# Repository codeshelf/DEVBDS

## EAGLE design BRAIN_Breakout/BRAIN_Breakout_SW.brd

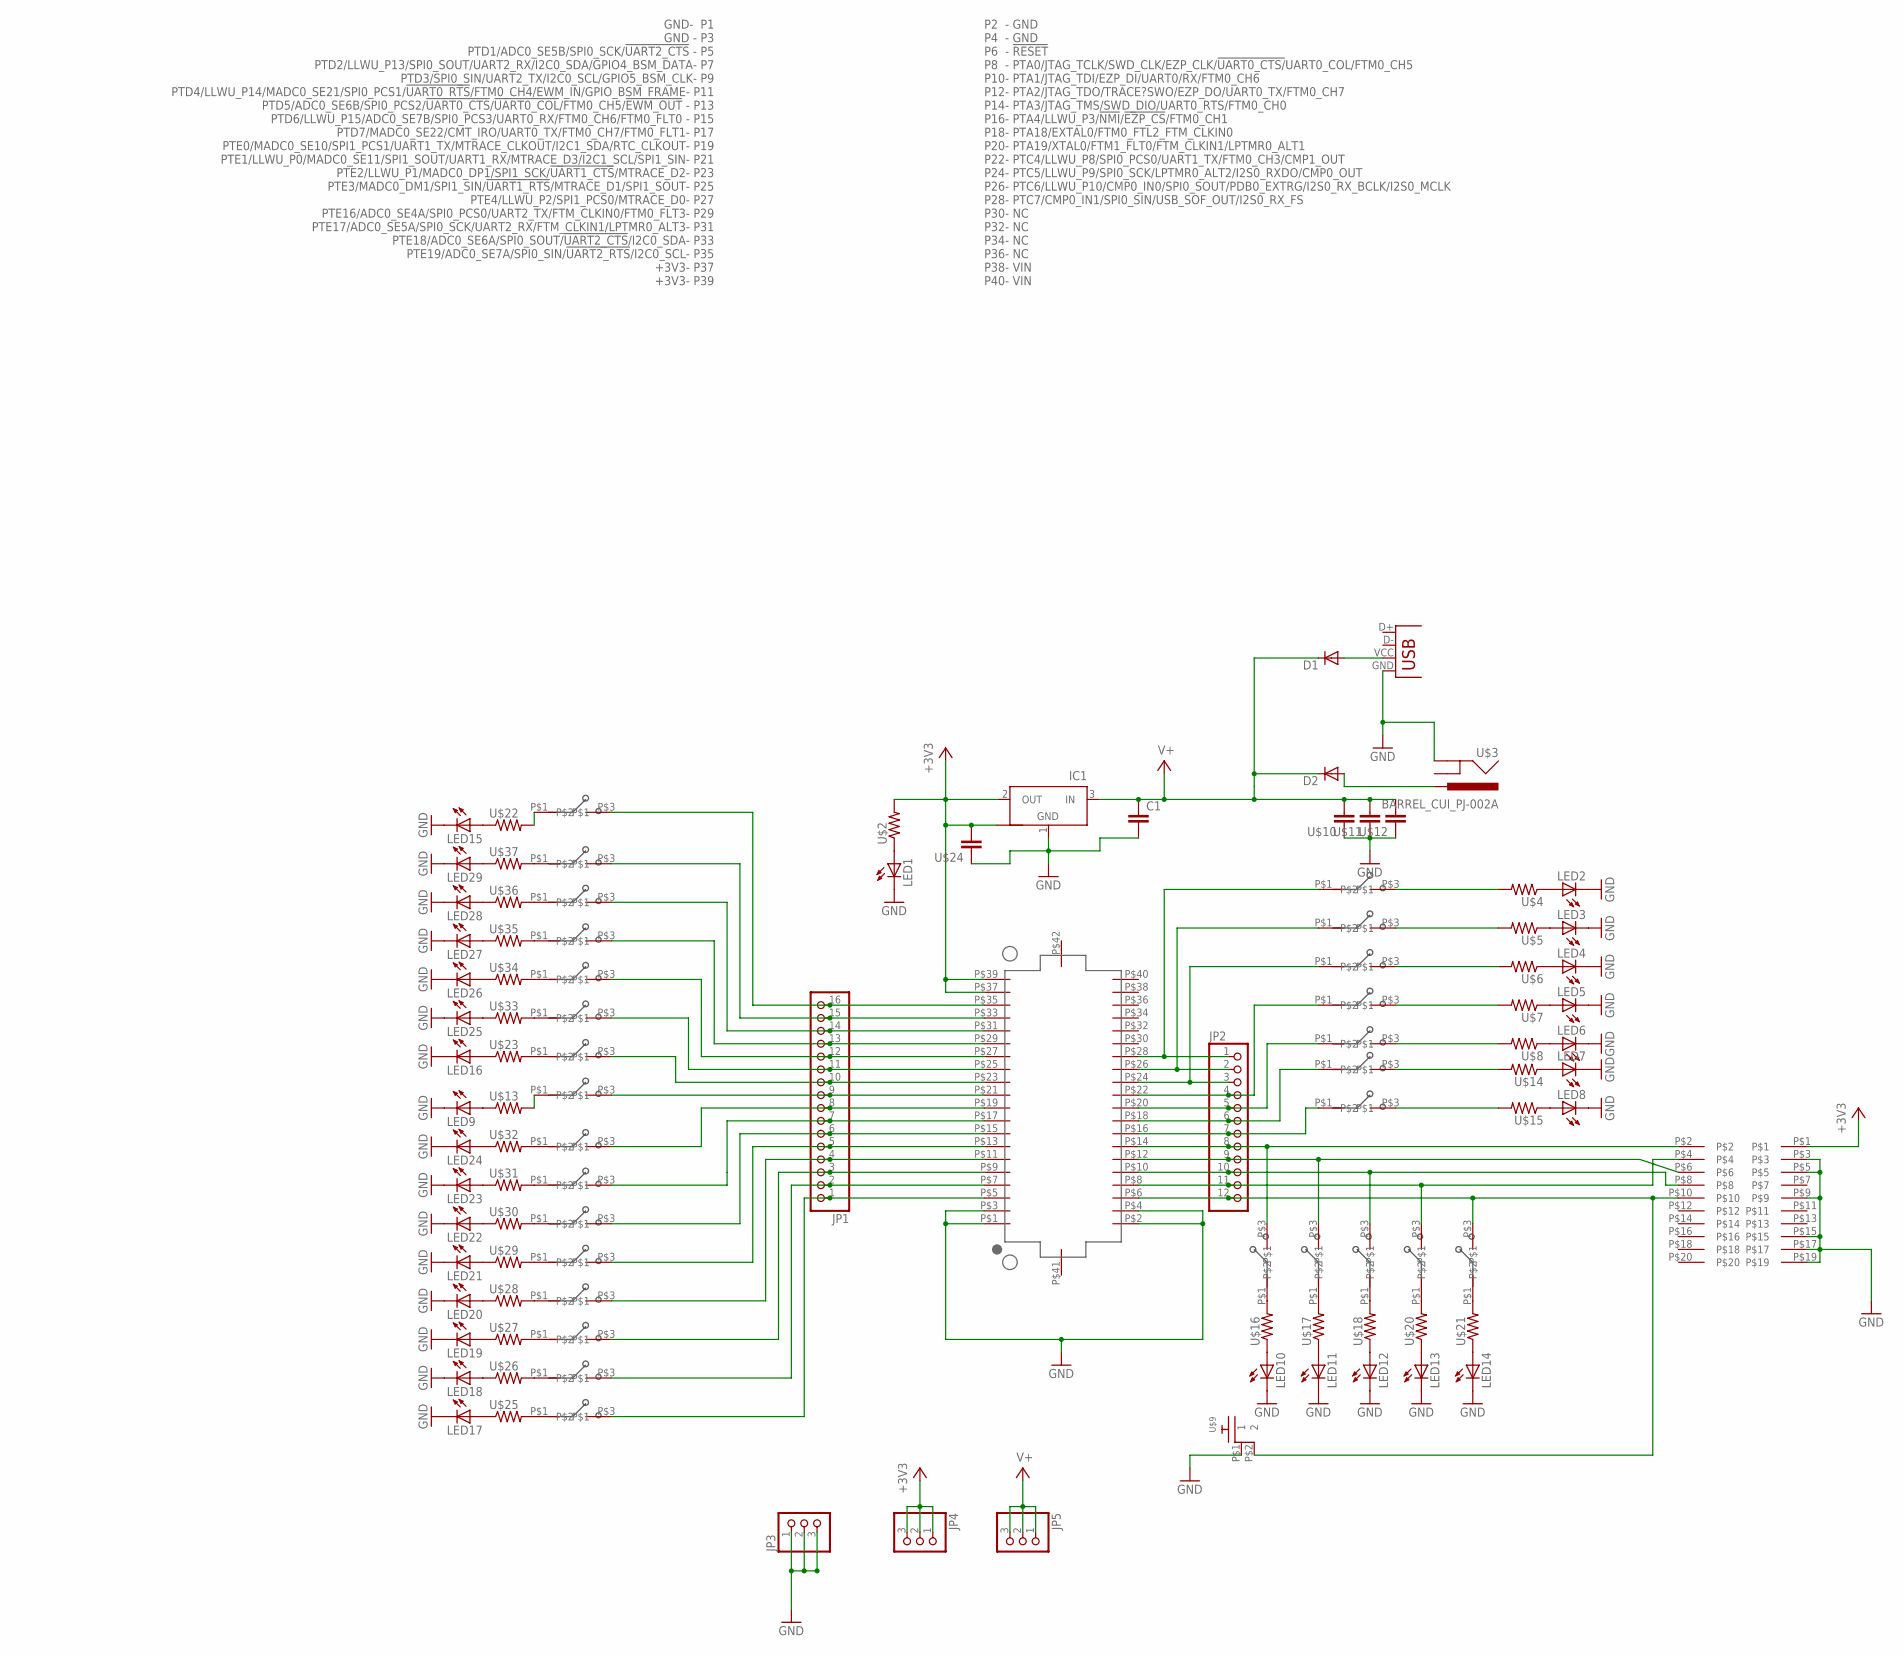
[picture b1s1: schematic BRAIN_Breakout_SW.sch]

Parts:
C1: RF-C0805; C0805
D1, D2: DIODESMA; SMA-DIODE
IC1: NCP1117ST33T3G_1; SOT223
JP1: PINHD-1X16; 1X16
JP2: PINHD-1X12; 1X12
JP3, JP4, JP5: PINHD-1X3; 1X03
LED1, LED2, LED3, LED4, LED5, LED6, LED7, LED8, LED9, LED10, LED11, LED12, LED13, LED14, LED15, LED16, LED17, LED18, LED19, LED20, LED21, LED22, LED23, LED24, LED25, LED26, LED27, LED28, LED29: LEDCHIP-LED0805; CHIP-LED0805
U$1: DF12_F
U$2, U$4, U$5, U$6, U$7, U$8, U$13, U$14, U$15, U$16, U$17, U$18, U$20, U$21, U$22, U$23, U$25, U$26, U$27, U$28, U$29, U$30, U$31, U$32, U$33, U$34, U$35, U$36, U$37: RF-R0805; RF-C0805
U$3: BARREL_CUI_PJ-002A
U$9: RA_BUTTON
U$10, U$11, U$12, U$24: RF-C0805; C0805
U$19: 2X10JTAG
U$38, U$39, U$40, U$41, U$42, U$43, U$44, U$45, U$46, U$47, U$48, U$49, U$50, U$51, U$52, U$53, U$54, U$55, U$56, U$57, U$58, U$59, U$60, U$61, U$62, U$63, U$64, U$65: CJS
X1: USB; USB3076-30-A

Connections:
+3V3: IC1.2 (OUT), IC1.4 (OUT1), JP4.1, JP4.2, JP4.3, U$1.P$37 (+3V3), U$1.P$39 (+3V3), U$2.2, U$19.P$1, U$24.2
GND: C1.2, IC1.1 (GND), JP3.1, JP3.2, JP3.3, LED1.C, LED2.C, LED3.C, LED4.C, LED5.C, LED6.C, LED7.C, LED8.C, LED9.C, LED10.C, LED11.C, LED12.C, LED13.C, LED14.C, LED15.C, LED16.C, LED17.C, LED18.C, LED19.C, LED20.C, LED21.C, LED22.C, LED23.C, LED24.C, LED25.C, LED26.C, LED27.C, LED28.C, LED29.C, U$1.P$1 (GND), U$1.P$2 (GND), U$1.P$3 (GND), U$1.P$4 (GND), U$3.P$2 (GND), U$9.P$1 (1), U$10.1, U$11.1, U$12.1, U$19.P$3, U$19.P$5, U$19.P$9, U$19.P$15, U$19.P$17, U$19.P$19, U$24.1, X1.GND
unnamed: LED1.A, U$2.1
unnamed: LED2.A, U$4.1
unnamed: LED3.A, U$5.1
unnamed: LED4.A, U$6.1
unnamed: LED8.A, U$15.1
unnamed: LED5.A, U$7.1
unnamed: LED6.A, U$8.1
unnamed: LED7.A, U$14.1
unnamed: LED9.A, U$13.1
unnamed: U$13.2, U$44.P$1
unnamed: U$15.2, U$65.P$3
unnamed: U$14.2, U$64.P$3
unnamed: U$8.2, U$63.P$3
unnamed: U$7.2, U$62.P$3
unnamed: U$6.2, U$61.P$3
unnamed: U$5.2, U$60.P$3
unnamed: U$4.2, U$59.P$3
unnamed: U$25.2, U$38.P$1
unnamed: U$26.2, U$39.P$1
unnamed: U$27.2, U$40.P$1
unnamed: JP2.1, U$1.P$28 (PTC7/CMP0_IN1/SPI0_SIN/USB_SOF_OUT/I2S0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), U$59.P$1
unnamed: JP2.2, U$1.P$26 (PTC6/LLWU_P10/CMP0_IN0/SPI0_SOUT/PDB0_E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), U$60.P$1
unnamed: JP2.3, U$1.P$24 (PTC5/LLWU_P8/SPI0_PCS0/UART1_TX/FTM0_CH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), U$61.P$1
unnamed: JP2.4, U$1.P$22 (PTC4/LLWU_P8/SPI0_PCS0/UART1_TX/FTM0_CH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), U$62.P$1
unnamed: JP2.5, U$1.P$20 (PTA19/XTAL0/FTM1_FLT0/FTM_CLKIN1/LPTMR0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), U$63.P$1
unnamed: JP2.6, U$1.P$18 (PTA18/EXTAL0/FTM0_FTL2_FTM_CLKIN0), U$64.P$1
unnamed: JP2.7, U$1.P$16 (PTA4/LLWU_P3/!NMI!/!EZP_CS!/FTM0_CH1), U$65.P$1
unnamed: LED15.A, U$22.1
unnamed: LED17.A, U$25.1
unnamed: LED18.A, U$26.1
unnamed: LED19.A, U$27.1
unnamed: LED20.A, U$28.1
unnamed: LED16.A, U$23.1
unnamed: LED25.A, U$33.1
unnamed: LED26.A, U$34.1
unnamed: LED27.A, U$35.1
unnamed: LED21.A, U$29.1
unnamed: LED22.A, U$30.1
unnamed: LED23.A, U$31.1
unnamed: LED24.A, U$32.1
unnamed: U$28.2, U$41.P$1
unnamed: U$29.2, U$42.P$1
unnamed: U$31.2, U$43.P$1
unnamed: U$37.2, U$46.P$1
unnamed: U$36.2, U$47.P$1
unnamed: LED28.A, U$36.1
unnamed: JP2.8, U$1.P$14 (PTA3/JTAG_TMS/SWD_DIO/UART0_RTS/FTM0_CH0), U$19.P$2, U$54.P$3
unnamed: LED10.A, U$16.1
unnamed: U$16.2, U$54.P$1
unnamed: JP2.9, U$1.P$12 (PTA2/JTAG_TDO/TRACE?SWO/EZP_DO/UART0_TX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), U$19.P$6, U$55.P$3
unnamed: LED11.A, U$17.1
unnamed: U$17.2, U$55.P$1
unnamed: JP2.10, U$1.P$10 (PTA1/JTAG_TDI/EZP_DI/UART0/RX/FTM0_CH6), U$19.P$8, U$56.P$3
unnamed: LED12.A, U$18.1
unnamed: U$18.2, U$56.P$1
unnamed: JP2.11, U$1.P$8 (PTA0/JTAG_TCLK/SWD_CLK/EZP_CLK/!UART0_C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), U$19.P$4, U$57.P$3
unnamed: LED13.A, U$20.1
unnamed: U$20.2, U$57.P$1
unnamed: JP2.12, U$1.P$6 (!RESET), U$9.P$2 (2), U$19.P$10, U$58.P$3
unnamed: LED14.A, U$21.1
unnamed: U$21.2, U$58.P$1
unnamed: LED29.A, U$37.1
unnamed: U$22.2, U$45.P$1
unnamed: U$35.2, U$48.P$1
unnamed: U$34.2, U$49.P$1
unnamed: U$33.2, U$50.P$1
unnamed: U$23.2, U$51.P$1
unnamed: U$32.2, U$52.P$1
unnamed: U$30.2, U$53.P$1
unnamed: D2.A, U$3.P$1 (PWR)
unnamed: D1.A, X1.VCC (VBUS)
PTD1: JP1.1, U$1.P$5 (PTD1/ADC0_SE5B/SPI0_SCK/!UART2_CTS), U$38.P$3
PTD2: JP1.2, U$1.P$7 (PTD2/LLWU_P13/SPI0_SOUT/UART2_RX/I2C0_S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), U$39.P$3
PTD3: JP1.3, U$1.P$9 (PTD3/SPI0_SIN/UART2_TX/I2C0_SCL/GPIO5_B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), U$40.P$3
PTD4: JP1.4, U$1.P$11 (PTD4/LLWU_P14/MADC0_SE21/SPI0_PCS1/!UAR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), U$41.P$3
PTD5: JP1.5, U$1.P$13 (PTD5/ADC0_SE6B/SPI0_PCS2/!UART0_CTS!/!U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), U$42.P$3
PTD6: JP1.6, U$1.P$15 (PTD6/LLWU_P15/ADC0_SE7B/SPI0_PCS3/UART0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), U$53.P$3
PTD7: JP1.7, U$1.P$17 (PTD7/MADC0_SE22/CMT_IRO/UART0_TX/FTM0_C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), U$43.P$3
PTE0: JP1.8, U$1.P$19 (PTE0/MADC0_SE10/SPI1_PCS1/UART1_TX/MTRA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), U$52.P$3
PTE1: JP1.9, U$1.P$21 (PTE1/LLWU_P0/MADC0_SE11/SPI1_SOUT/UART1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), U$44.P$3
PTE2: JP1.10, U$1.P$23 (PTE2/LLWU_P1/MADC0_DP1/SPI1_SCK/!UART1_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), U$51.P$3
PTE3: JP1.11, U$1.P$25 (PTE3/MADC0_DM1/SPI1_SIN/!UART1_RTS!/MTR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), U$50.P$3
PTE4: JP1.12, U$1.P$27 (PTE4/LLWU_P2/SPI1_PCS0/MTRACE_D0), U$49.P$3
PTE16: JP1.13, U$1.P$29 (PTE16/ADC0_SE4A/SPI0_PCS0/UART2_TX/FTM_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), U$48.P$3
PTE17: JP1.14, U$1.P$31 (PTE17/ADC0_SE5A/SPI0_SCK/UART2_RX/FTM_C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), U$47.P$3
PTE18: JP1.15, U$1.P$33 (PTE18/ADC0_SE6A/SPI0_SOUT/!UART2_CTS!/I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), U$46.P$3
PTE19: JP1.16, U$1.P$35 (PTE19/ADC0_SE7A/SPI0_SIN/!UART2_RTS!/I2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), U$45.P$3
V+: C1.1, D1.C, D2.C, IC1.3 (IN), JP5.1, JP5.2, JP5.3, U$10.2, U$11.2, U$12.2

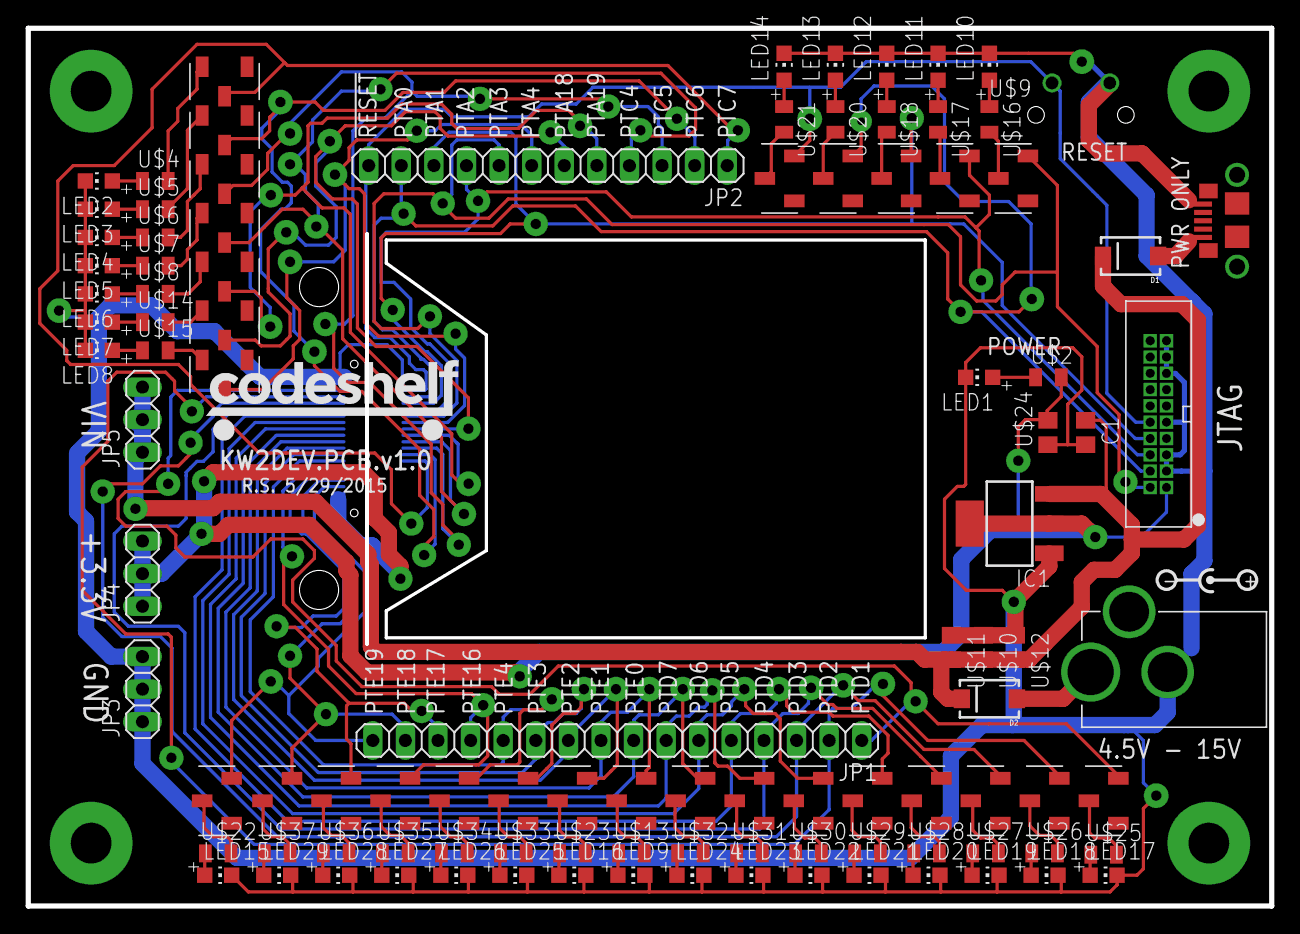
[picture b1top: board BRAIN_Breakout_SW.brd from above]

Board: 2 copper layers, 96.9 x 68.4 mm, 104 parts (1 on the bottom side), 90 nets.

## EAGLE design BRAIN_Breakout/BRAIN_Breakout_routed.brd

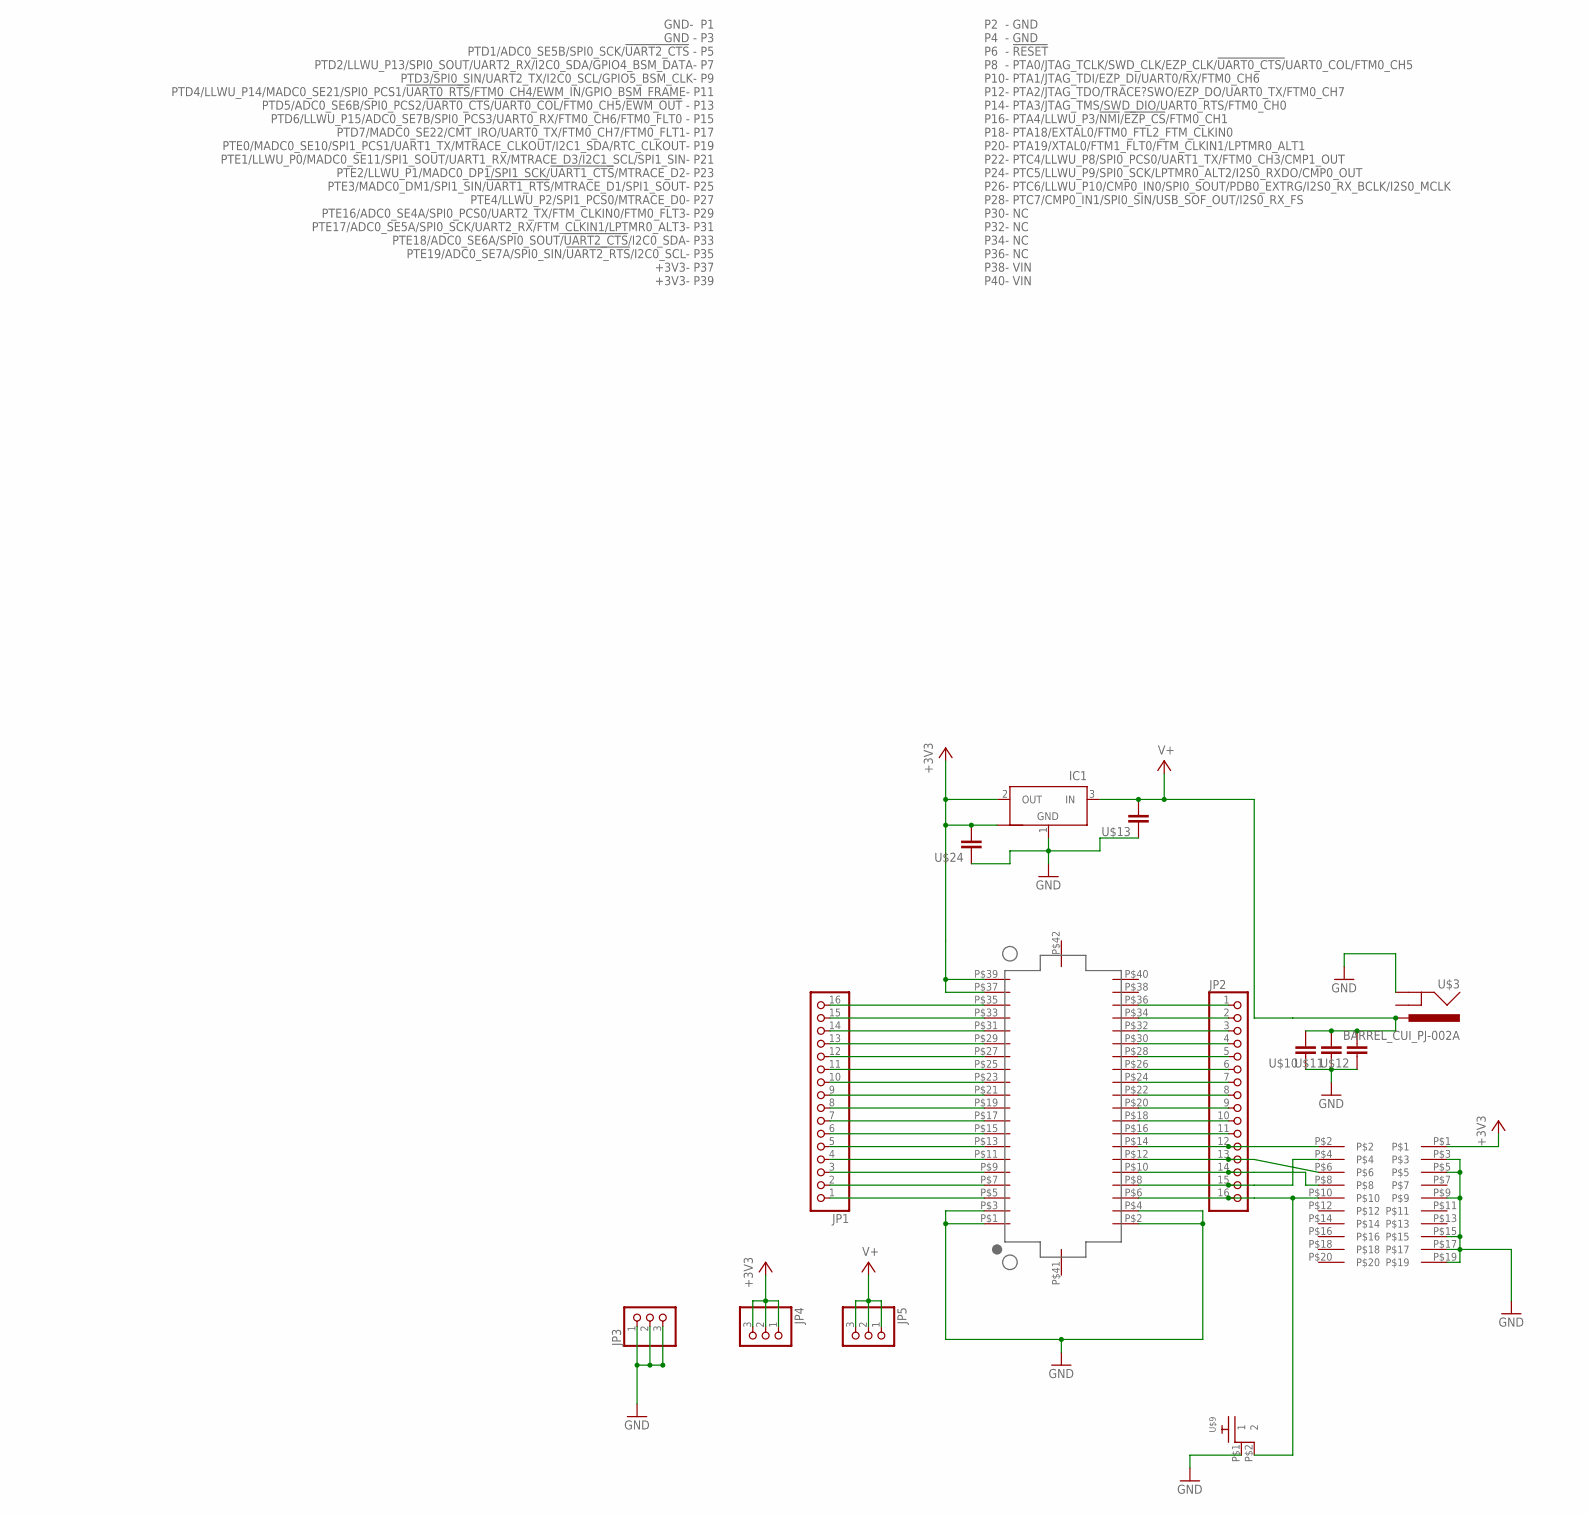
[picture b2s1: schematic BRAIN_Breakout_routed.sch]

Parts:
IC1: NCP1117ST33T3G_1; SOT223
JP1, JP2: PINHD-1X16; 1X16
JP3, JP4, JP5: PINHD-1X3; 1X03
U$1: DF12_F
U$3: BARREL_CUI_PJ-002A
U$9: RA_BUTTON
U$10, U$11, U$12, U$13, U$24: RF-C0805; C0805
U$19: 2X10JTAG

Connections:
+3V3: IC1.2 (OUT), IC1.4 (OUT1), JP4.1, JP4.2, JP4.3, U$1.P$37 (+3V3), U$1.P$39 (+3V3), U$19.P$1, U$24.2
GND: IC1.1 (GND), JP3.1, JP3.2, JP3.3, U$1.P$1 (GND), U$1.P$2 (GND), U$1.P$3 (GND), U$1.P$4 (GND), U$3.P$2 (GND), U$9.P$1 (1), U$10.1, U$11.1, U$12.1, U$13.1, U$19.P$3, U$19.P$5, U$19.P$9, U$19.P$15, U$19.P$17, U$19.P$19, U$24.1
unnamed: JP2.1, U$1.P$36 (NC)
unnamed: JP2.2, U$1.P$34 (NC)
unnamed: JP2.3, U$1.P$32 (NC)
unnamed: JP2.4, U$1.P$30 (NC)
unnamed: JP2.5, U$1.P$28 (PTC7/CMP0_IN1/SPI0_SIN/USB_SOF_OUT/I2S0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)
unnamed: JP2.6, U$1.P$26 (PTC6/LLWU_P10/CMP0_IN0/SPI0_SOUT/PDB0_E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)
unnamed: JP2.7, U$1.P$24 (PTC5/LLWU_P8/SPI0_PCS0/UART1_TX/FTM0_CH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)
unnamed: JP2.8, U$1.P$22 (PTC4/LLWU_P8/SPI0_PCS0/UART1_TX/FTM0_CH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)
unnamed: JP2.9, U$1.P$20 (PTA19/XTAL0/FTM1_FLT0/FTM_CLKIN1/LPTMR0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)
unnamed: JP2.10, U$1.P$18 (PTA18/EXTAL0/FTM0_FTL2_FTM_CLKIN0)
unnamed: JP2.11, U$1.P$16 (PTA4/LLWU_P3/!NMI!/!EZP_CS!/FTM0_CH1)
unnamed: JP2.16, U$1.P$6 (!RESET), U$9.P$2 (2), U$19.P$10
unnamed: JP2.15, U$1.P$8 (PTA0/JTAG_TCLK/SWD_CLK/EZP_CLK/!UART0_C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), U$19.P$4
unnamed: JP2.14, U$1.P$10 (PTA1/JTAG_TDI/EZP_DI/UART0/RX/FTM0_CH6), U$19.P$8
unnamed: JP2.12, U$1.P$14 (PTA3/JTAG_TMS/SWD_DIO/UART0_RTS/FTM0_CH0), U$19.P$2
unnamed: JP2.13, U$1.P$12 (PTA2/JTAG_TDO/TRACE?SWO/EZP_DO/UART0_TX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), U$19.P$6
PTD1: JP1.1, U$1.P$5 (PTD1/ADC0_SE5B/SPI0_SCK/!UART2_CTS)
PTD2: JP1.2, U$1.P$7 (PTD2/LLWU_P13/SPI0_SOUT/UART2_RX/I2C0_S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)
PTD3: JP1.3, U$1.P$9 (PTD3/SPI0_SIN/UART2_TX/I2C0_SCL/GPIO5_B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)
PTD4: JP1.4, U$1.P$11 (PTD4/LLWU_P14/MADC0_SE21/SPI0_PCS1/!UAR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)
PTD5: JP1.5, U$1.P$13 (PTD5/ADC0_SE6B/SPI0_PCS2/!UART0_CTS!/!U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)
PTD6: JP1.6, U$1.P$15 (PTD6/LLWU_P15/ADC0_SE7B/SPI0_PCS3/UART0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)
PTD7: JP1.7, U$1.P$17 (PTD7/MADC0_SE22/CMT_IRO/UART0_TX/FTM0_C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)
PTE0: JP1.8, U$1.P$19 (PTE0/MADC0_SE10/SPI1_PCS1/UART1_TX/MTRA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)
PTE1: JP1.9, U$1.P$21 (PTE1/LLWU_P0/MADC0_SE11/SPI1_SOUT/UART1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)
PTE2: JP1.10, U$1.P$23 (PTE2/LLWU_P1/MADC0_DP1/SPI1_SCK/!UART1_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)
PTE3: JP1.11, U$1.P$25 (PTE3/MADC0_DM1/SPI1_SIN/!UART1_RTS!/MTR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)
PTE4: JP1.12, U$1.P$27 (PTE4/LLWU_P2/SPI1_PCS0/MTRACE_D0)
PTE16: JP1.13, U$1.P$29 (PTE16/ADC0_SE4A/SPI0_PCS0/UART2_TX/FTM_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)
PTE17: JP1.14, U$1.P$31 (PTE17/ADC0_SE5A/SPI0_SCK/UART2_RX/FTM_C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)
PTE18: JP1.15, U$1.P$33 (PTE18/ADC0_SE6A/SPI0_SOUT/!UART2_CTS!/I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)
PTE19: JP1.16, U$1.P$35 (PTE19/ADC0_SE7A/SPI0_SIN/!UART2_RTS!/I2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)
V+: IC1.3 (IN), JP5.1, JP5.2, JP5.3, U$3.P$1 (PWR), U$10.2, U$11.2, U$12.2, U$13.2

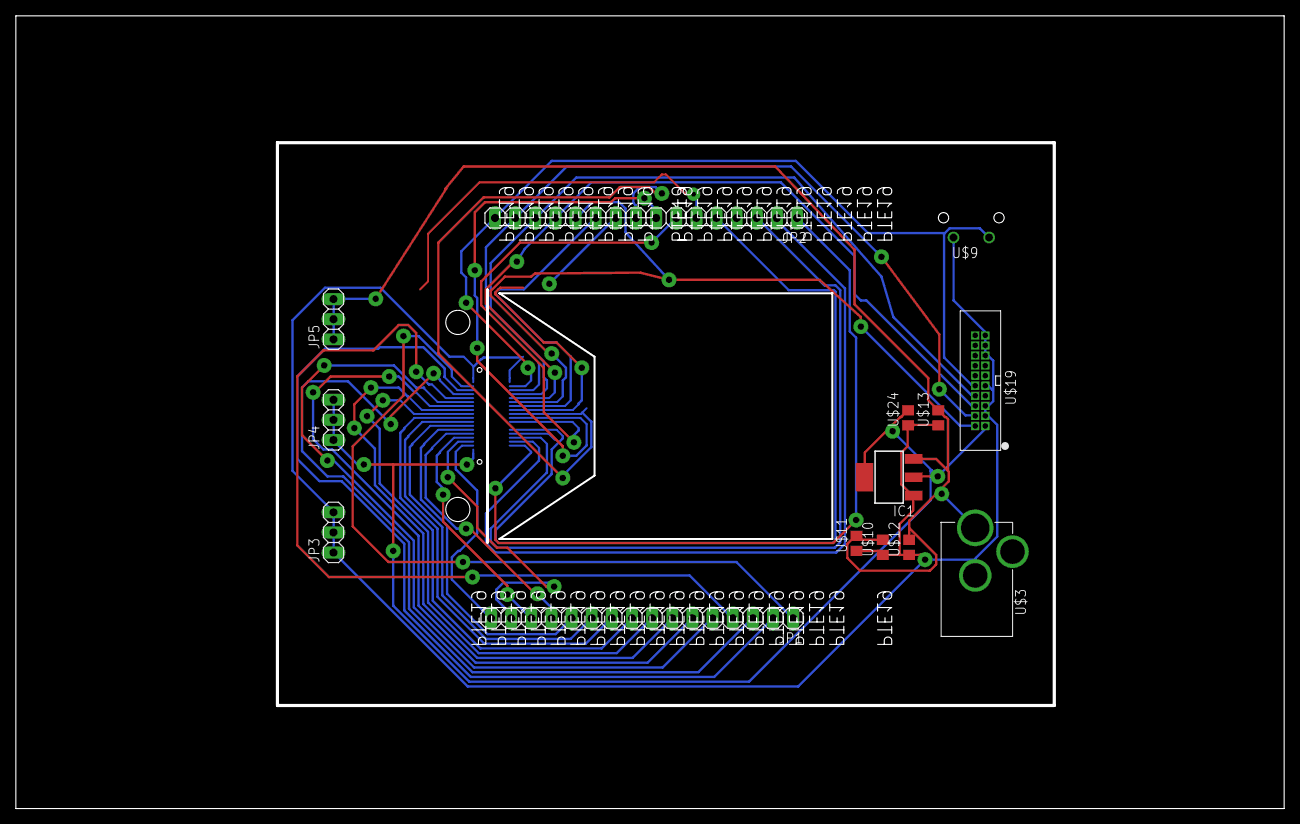
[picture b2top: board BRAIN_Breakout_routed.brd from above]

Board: 2 copper layers, 160.0 x 100.0 mm, 15 parts (1 on the bottom side), 35 nets.

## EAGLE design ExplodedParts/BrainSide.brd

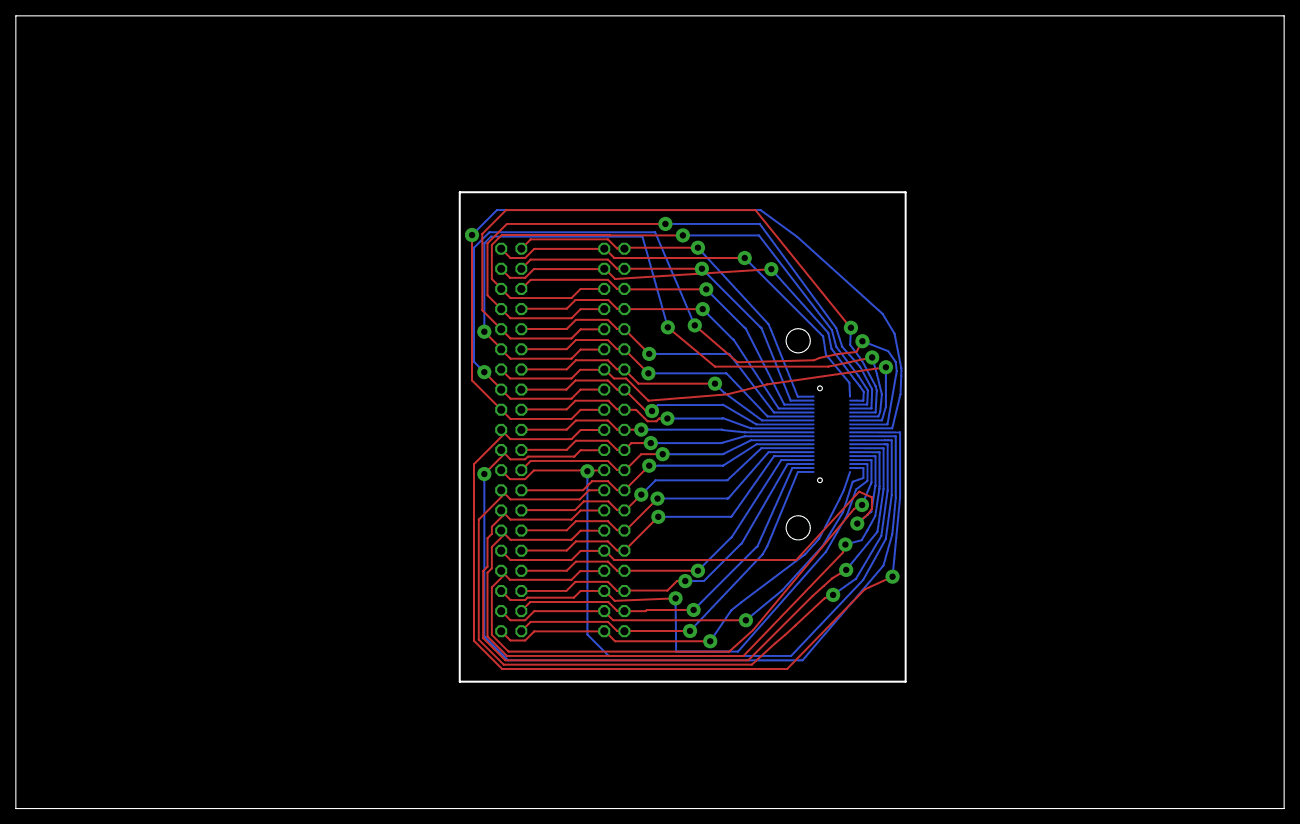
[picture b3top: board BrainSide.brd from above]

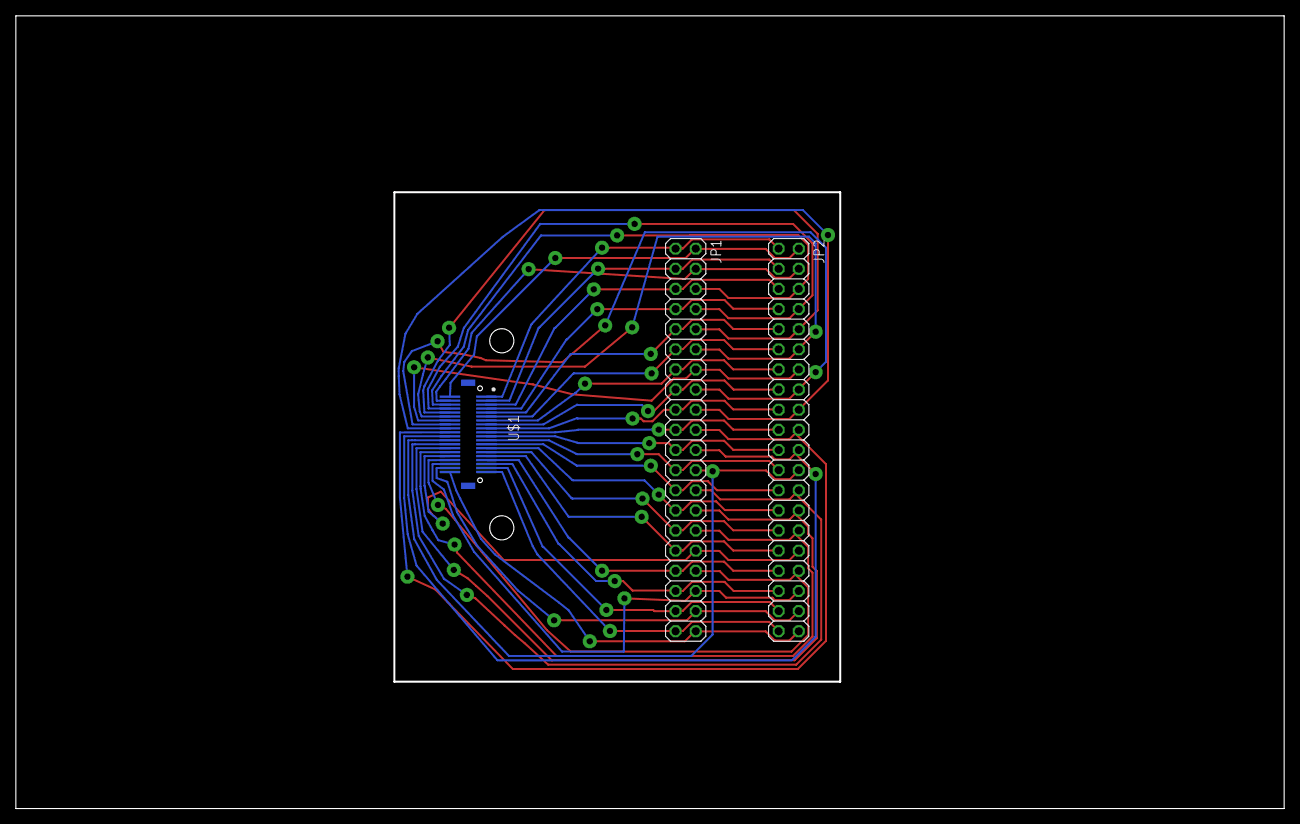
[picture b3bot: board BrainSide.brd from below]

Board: 2 copper layers, 160.0 x 100.0 mm, 3 parts (3 on the bottom side), 40 nets.

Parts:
JP1, JP2: 2X20
U$1: DF12_F

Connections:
unnamed: JP1.39, JP2.39, U$1.P$39
unnamed: JP1.37, JP2.37, U$1.P$37
unnamed: JP1.35, JP2.35, U$1.P$35
unnamed: JP1.33, JP2.33, U$1.P$33
unnamed: JP1.31, JP2.31, U$1.P$31
unnamed: JP1.29, JP2.29, U$1.P$29
unnamed: JP1.27, JP2.27, U$1.P$27
unnamed: JP1.25, JP2.25, U$1.P$25
unnamed: JP1.23, JP2.23, U$1.P$23
unnamed: JP1.21, JP2.21, U$1.P$21
unnamed: JP1.19, JP2.19, U$1.P$19
unnamed: JP1.17, JP2.17, U$1.P$17
unnamed: JP1.15, JP2.15, U$1.P$15
unnamed: JP1.13, JP2.13, U$1.P$13
unnamed: JP1.11, JP2.11, U$1.P$11
unnamed: JP1.9, JP2.9, U$1.P$9
unnamed: JP1.7, JP2.7, U$1.P$7
unnamed: JP1.5, JP2.5, U$1.P$5
unnamed: JP1.3, JP2.3, U$1.P$3
unnamed: JP1.1, JP2.1, U$1.P$1
unnamed: JP1.2, JP2.2, U$1.P$2
unnamed: JP1.4, JP2.4, U$1.P$4
unnamed: JP1.6, JP2.6, U$1.P$6
unnamed: JP1.8, JP2.8, U$1.P$8
unnamed: JP1.10, JP2.10, U$1.P$10
unnamed: JP1.12, JP2.12, U$1.P$12
unnamed: JP1.14, JP2.14, U$1.P$14
unnamed: JP1.16, JP2.16, U$1.P$16
unnamed: JP1.18, JP2.18, U$1.P$18
unnamed: JP1.20, JP2.20, U$1.P$20
unnamed: JP1.22, JP2.22, U$1.P$22
unnamed: JP1.24, JP2.24, U$1.P$24
unnamed: JP1.26, JP2.26, U$1.P$26
unnamed: JP1.28, JP2.28, U$1.P$28
unnamed: JP1.30, JP2.30, U$1.P$30
unnamed: JP1.32, JP2.32, U$1.P$32
unnamed: JP1.34, JP2.34, U$1.P$34
unnamed: JP1.36, JP2.36, U$1.P$36
unnamed: JP1.38, JP2.38, U$1.P$38
unnamed: JP1.40, JP2.40, U$1.P$40

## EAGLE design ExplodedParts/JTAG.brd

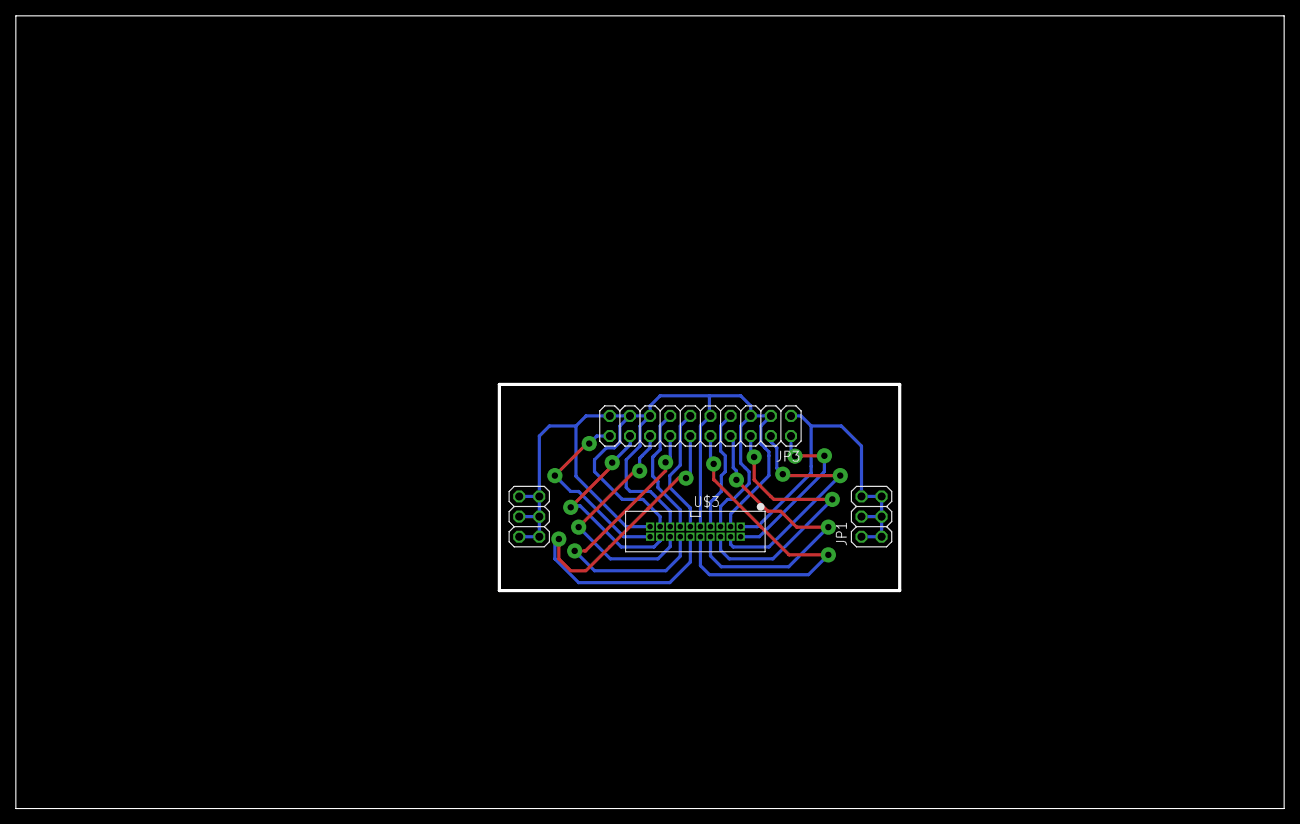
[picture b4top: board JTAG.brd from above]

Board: 2 copper layers, 160.0 x 100.0 mm, 4 parts (0 on the bottom side), 15 nets.

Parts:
JP1, JP2: 2X03
JP3: 2X10
U$3: 2X10JTAG

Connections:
unnamed: JP1.1, JP1.2, JP1.3, JP1.4, JP1.5, JP1.6, JP3.1, U$3.P$1
unnamed: JP3.2, U$3.P$2
unnamed: JP3.4, U$3.P$4
unnamed: JP3.6, U$3.P$6
unnamed: JP3.8, U$3.P$8
unnamed: JP3.10, U$3.P$10
unnamed: JP3.12, U$3.P$12
unnamed: JP3.14, U$3.P$14
unnamed: JP3.16, U$3.P$16
unnamed: JP3.18, U$3.P$18
unnamed: JP3.20, U$3.P$20
unnamed: JP2.1, JP2.2, JP2.3, JP2.4, JP2.5, JP2.6, JP3.3, JP3.5, JP3.9, JP3.15, JP3.17, JP3.19, U$3.P$3, U$3.P$5, U$3.P$9, U$3.P$15, U$3.P$17, U$3.P$19
unnamed: JP3.7, U$3.P$7
unnamed: JP3.11, U$3.P$11
unnamed: JP3.13, U$3.P$13

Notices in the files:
parts and their libraries:
SparkFun: Licensing: CC v3.0 Share-Alike You are welcome to use this library for commercial purposes.
